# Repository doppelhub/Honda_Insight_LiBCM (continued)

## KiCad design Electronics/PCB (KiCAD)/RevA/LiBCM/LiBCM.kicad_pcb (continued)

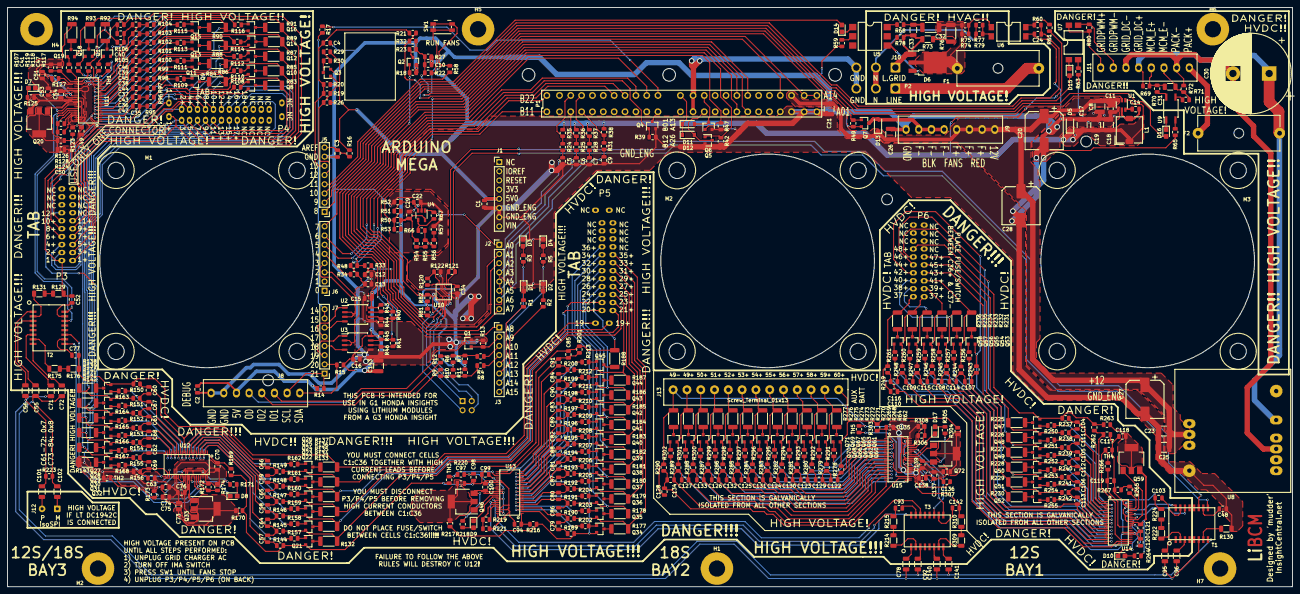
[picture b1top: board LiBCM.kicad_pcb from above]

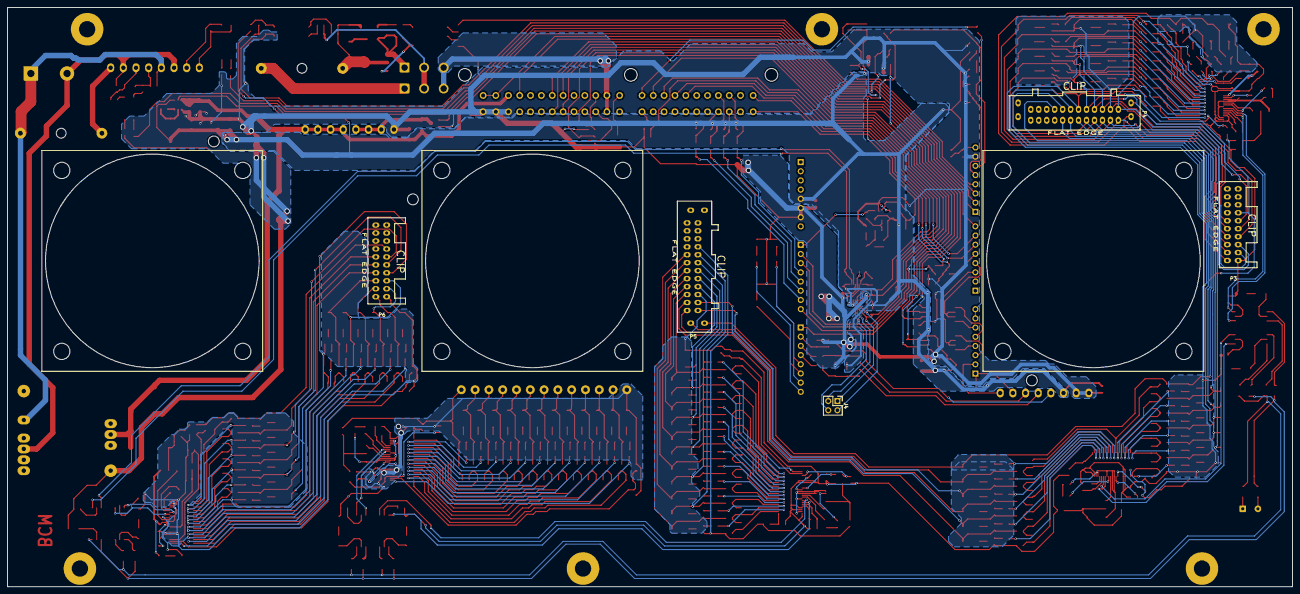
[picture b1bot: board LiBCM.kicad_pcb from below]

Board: 4 copper layers, 355.0 x 160.0 mm, 597 parts (5 on the bottom side), 517 nets.
